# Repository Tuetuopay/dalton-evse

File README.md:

# OSS EVSE

I hope you like the daltons!

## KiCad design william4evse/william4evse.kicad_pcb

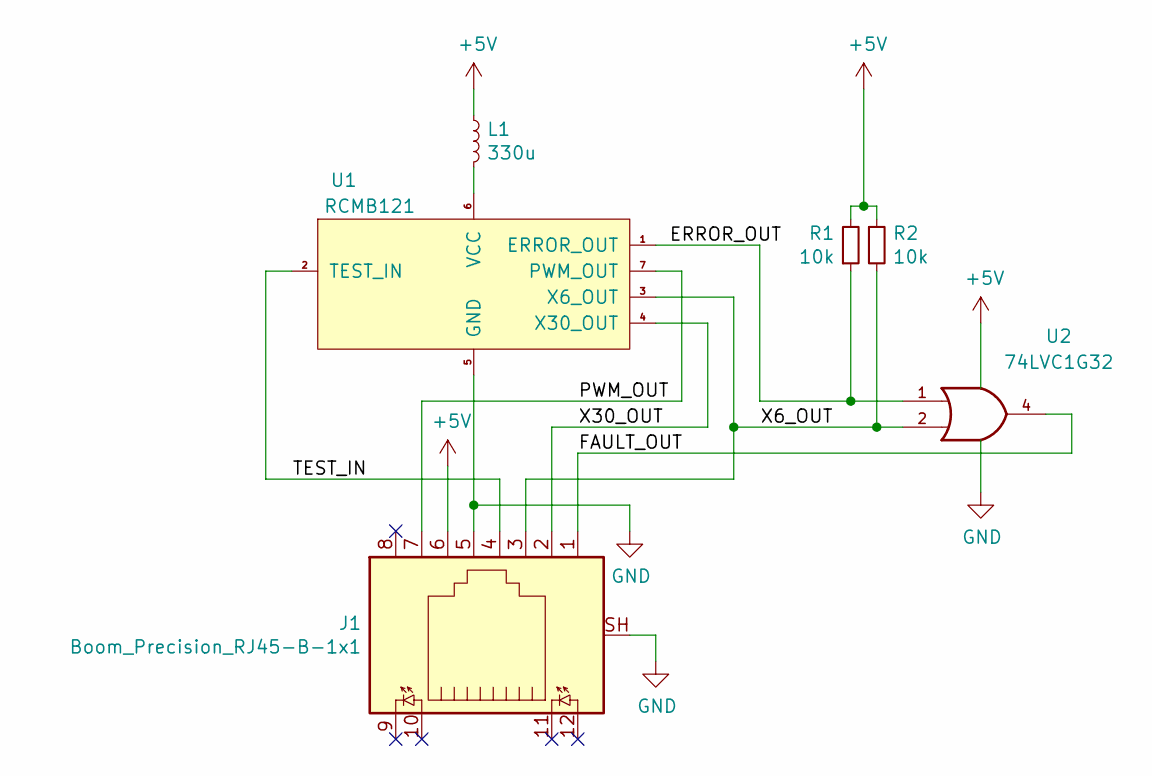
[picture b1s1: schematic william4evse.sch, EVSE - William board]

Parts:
J1: Boom_Precision_RJ45-B-1x1; RJ45_Amphenol_RJHSE538X
L1: 330u; L_1210_3225Metric; MFR P/N NLCV32T-331K-PF; LCSC P/N C87557
R1, R2: 10k; R_0603_1608Metric; MFR P/N 0603WAF1002T5E; LCSC P/N C25804
U1: RCMB121
U2: 74LVC1G32; SOT-353_SC-70-5; MFR P/N 74LVC1G32GW,125; LCSC P/N C12516

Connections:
+5V: J1.6, L1.1, R1.2, R2.1, U2.5 (VCC)
/ERROR_OUT: R1.1, U1.1 (ERROR_OUT), U2.1
/FAULT_OUT: J1.1, U2.4
/PWM_OUT: J1.7, U1.7 (PWM_OUT)
/TEST_IN: J1.4, U1.2 (TEST_IN)
/X6_OUT: J1.3, R2.2, U1.3 (X6_OUT), U2.2
/X30_OUT: J1.2, U1.4 (X30_OUT)
GND: J1.5, J1.SH, U1.5 (GND), U2.3 (GND)
unnamed: L1.2, U1.6 (VCC)

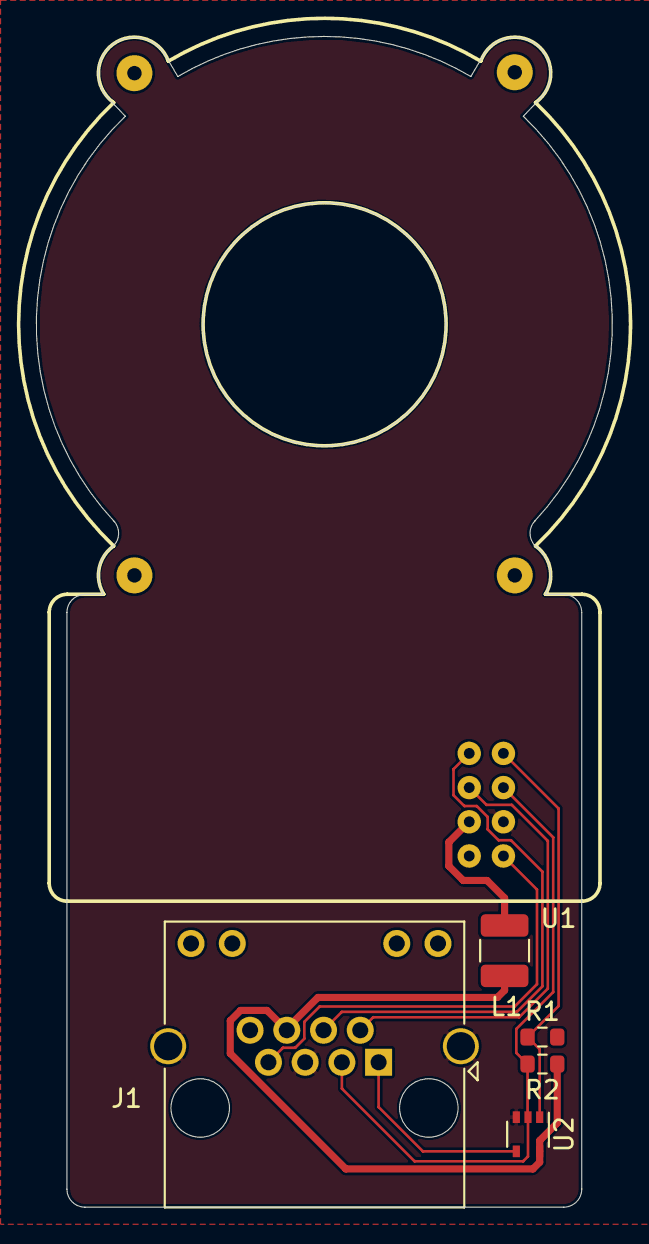
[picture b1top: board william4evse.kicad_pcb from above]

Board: 2 copper layers, 32.0 x 65.0 mm, 6 parts (0 on the bottom side), 9 nets.

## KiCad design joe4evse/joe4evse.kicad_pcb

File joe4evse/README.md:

# joe4evse

Joe, the brain of the operation. Main PCB of Daltons EVSE

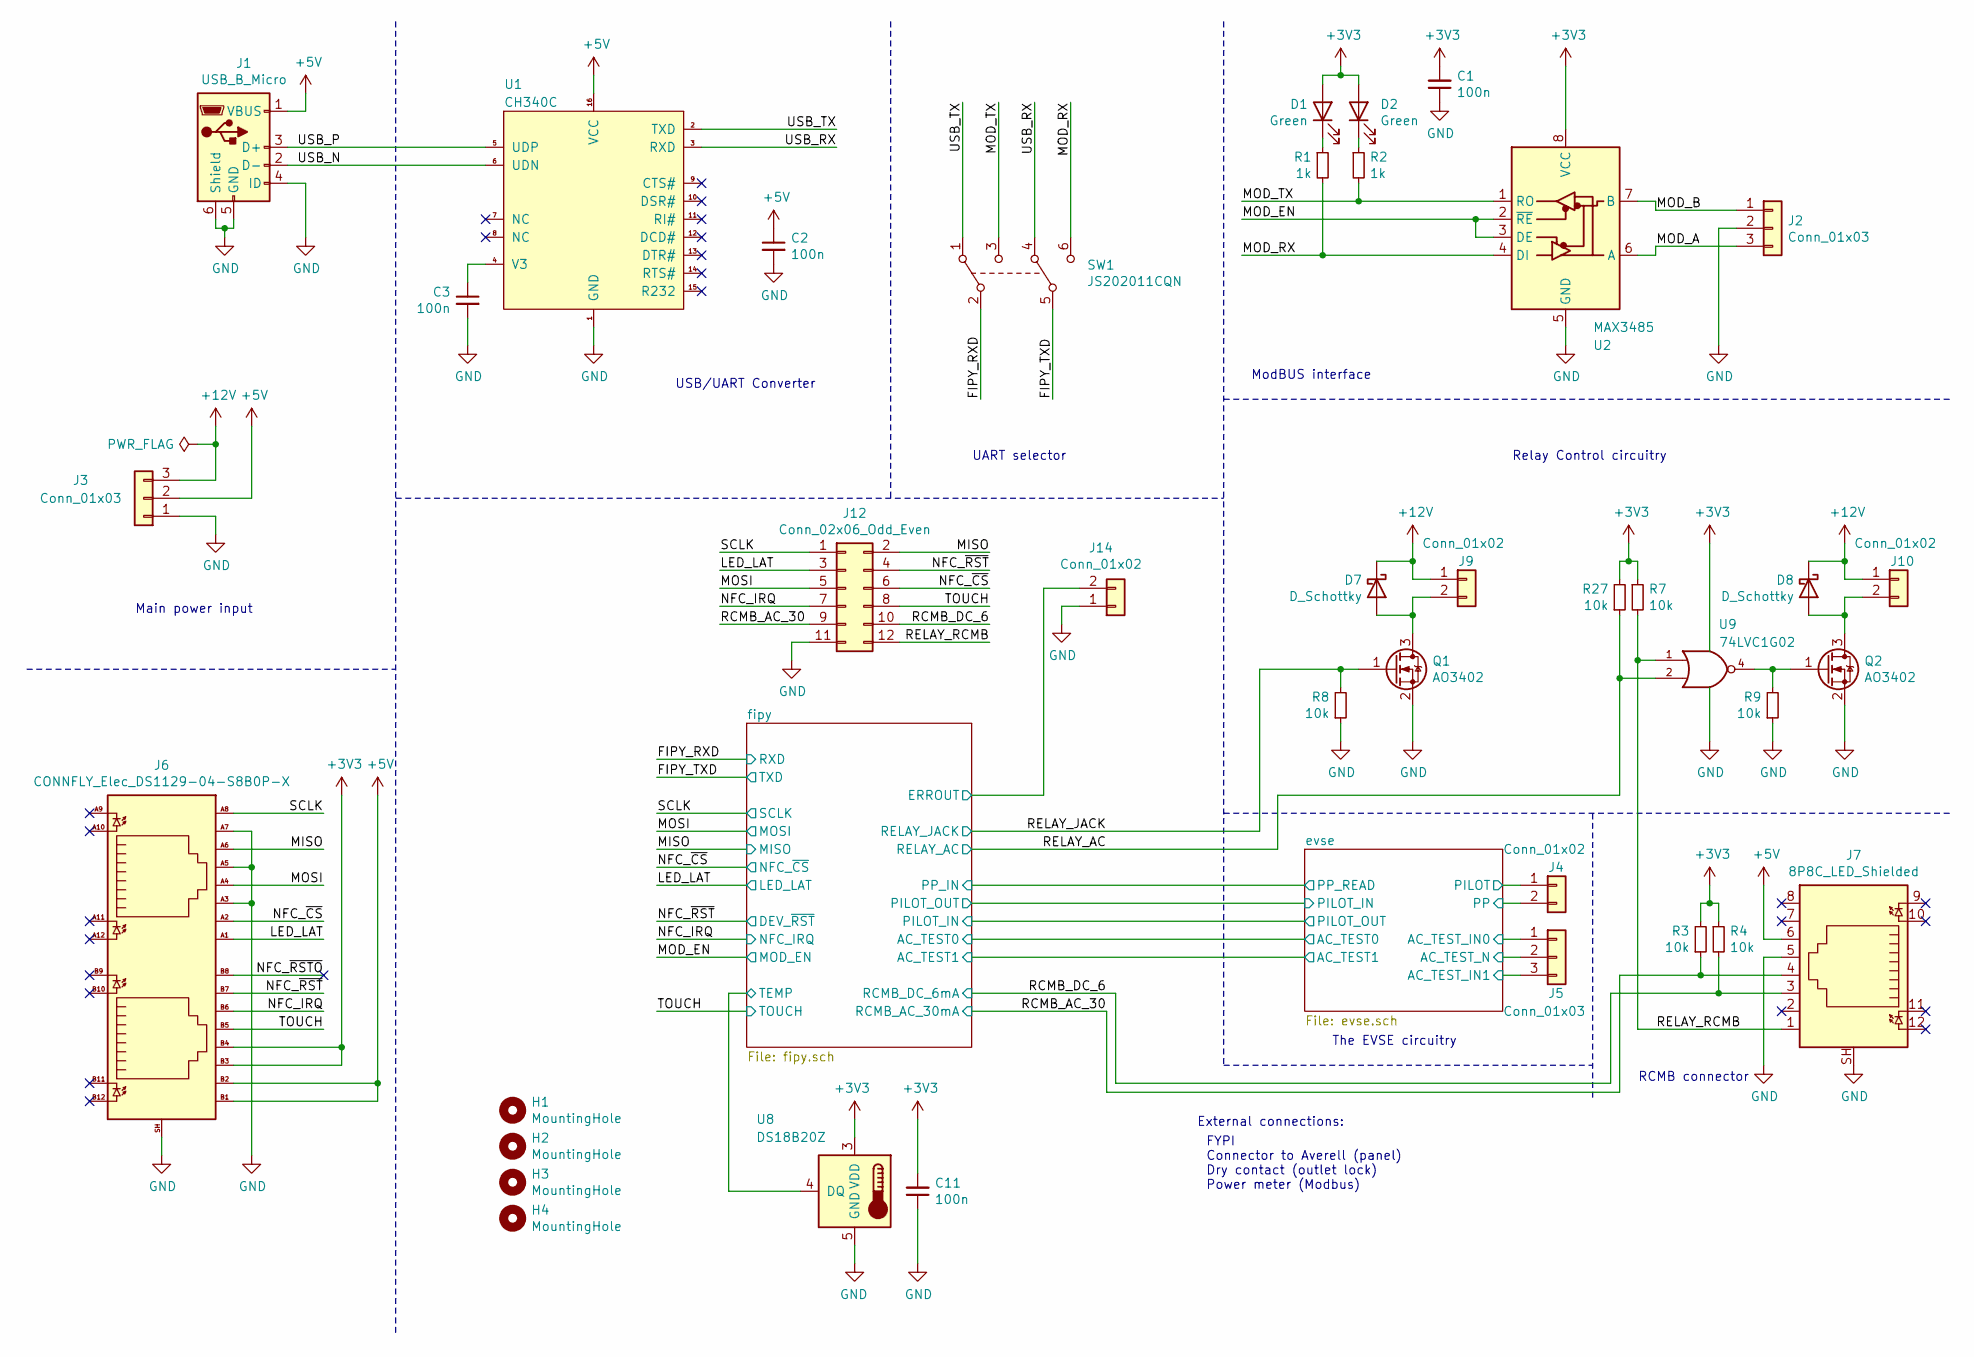
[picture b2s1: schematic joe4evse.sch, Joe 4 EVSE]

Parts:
C1, C2, C3, C11: 100n; C_0603_1608Metric
D1, D2: Green; LED_0603_1608Metric
D7, D8: D_Schottky; D_SOD-123
H1, H2, H3, H4: MountingHole; MountingHole_3.2mm_M3_Pad_Via
J1: USB_B_Micro; USB_Micro-B_Molex_47346-0001
J2: Conn_01x03; JST_PH_B3B-PH-K_1x03_P2.00mm_Vertical
J3: Conn_01x03; JST_EH_B3B-EH-A_1x03_P2.50mm_Vertical
J4, J9, J10, J14: Conn_01x02; JST_PH_B2B-PH-K_1x02_P2.00mm_Vertical
J5: Conn_01x03; JST_NV_B03P-NV_1x03_P5.00mm_Vertical
J6: CONNFLY_Elec_DS1129-04-S8B0P-X
J7: 8P8C_LED_Shielded; RJ45_Amphenol_RJHSE538X
J12: Conn_02x06_Odd_Even; PinHeader_2x06_P2.54mm_Vertical
Q1, Q2: AO3402; SOT-23
R1, R2: 1k; R_0603_1608Metric
R3, R4, R7, R8, R9, R27: 10k; R_0603_1608Metric
SW1: JS202011CQN
U1: CH340C; SOIC-16_3.9x9.9mm_P1.27mm
U2: MAX3485; SOIC-8_3.9x4.9mm_P1.27mm
U8: DS18B20Z; SOIC-8_3.9x4.9mm_P1.27mm
U9: 74LVC1G02; SOT-353_SC-70-5

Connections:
+3V3: C1.2, C11.2, D1.2 (A), D2.2 (A), J6.B3, J6.B4, R3.2, R4.1, R7.1, R27.2, U2.8 (VCC), U8.3 (VDD), U9.5 (VCC); also elsewhere on the board
+5V: C2.1, J1.1 (VBUS), J3.2, J6.B1, J6.B2, J7.6, U1.16 (VCC); also elsewhere on the board
+12V: D7.1 (K), D8.1 (K), J3.3, J9.1, J10.1; also elsewhere on the board
/FIPY_RXD: SW1.2 (B1); also elsewhere on the board
/FIPY_TXD: SW1.5 (B2); also elsewhere on the board
/LED_LAT: J6.A1, J12.3; also elsewhere on the board
/MISO: J6.A6, J12.2; also elsewhere on the board
/MOD_A: J2.3, U2.6 (A)
/MOD_B: J2.1, U2.7 (B)
/MOD_EN: U2.2 (~RE), U2.3 (DE); also elsewhere on the board
/MOD_RX: R1.2, SW1.6 (C2), U2.4 (DI)
/MOD_TX: R2.2, SW1.3 (C1), U2.1 (RO)
/MOSI: J6.A4, J12.5; also elsewhere on the board
/NFC_IRQ: J6.B6, J12.7; also elsewhere on the board
/NFC_~CS: J6.A2, J12.6; also elsewhere on the board
/NFC_~RST: J6.B7, J12.4; also elsewhere on the board
/NFC_~RSTO: J6.B8
/RCMB_AC_30: J7.4, J12.9, R3.1; also elsewhere on the board
/RCMB_DC_6: J7.3, J12.10, R4.2; also elsewhere on the board
/RELAY_AC: R27.1, U9.2; also elsewhere on the board
/RELAY_JACK: Q1.1 (G), R8.2; also elsewhere on the board
/RELAY_RCMB: J7.1, J12.12, R7.2, U9.1
/SCLK: J6.A8, J12.1; also elsewhere on the board
/TOUCH: J6.B5, J12.8; also elsewhere on the board
/USB_N: J1.2 (D-), U1.6 (UDN)
/USB_P: J1.3 (D+), U1.5 (UDP)
/USB_RX: SW1.4 (A2), U1.3 (RXD)
/USB_TX: SW1.1 (A1), U1.2 (TXD)
/evse/AC_TEST_IN0: J5.1; also elsewhere on the board
/evse/AC_TEST_IN1: J5.3; also elsewhere on the board
/evse/AC_TEST_N: J5.2; also elsewhere on the board
/evse/PILOT: J4.1; also elsewhere on the board
/evse/PP: J4.2; also elsewhere on the board
/fipy/ERROUT: J14.2; also elsewhere on the board
/fipy/TEMP: U8.4 (DQ); also elsewhere on the board
GND: C1.1, C2.2, C3.2, C11.1, J1.4 (ID), J1.5 (GND), J1.6 (Shield), J2.2, J3.1, J6.A3, J6.A5, J6.A7, J6.SH, J7.5, J7.SH, J12.11, J14.1, Q1.2 (S), Q2.2 (S), R8.1, R9.1, U1.1 (GND), U2.5 (GND), U8.5 (GND), U9.3 (GND); also elsewhere on the board
unnamed: C3.1, U1.4 (V3)
unnamed: D1.1 (K), R1.1
unnamed: D2.1 (K), R2.1
unnamed: D7.2 (A), J9.2, Q1.3 (D)
unnamed: D8.2 (A), J10.2, Q2.3 (D)
unnamed: Q2.1 (G), R9.2, U9.4

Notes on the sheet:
Main power input
USB/UART Converter
UART selector
ModBUS interface
External connections:
FYPI Connector to Averell (panel) Dry contact (outlet lock) Power meter (Modbus)
RCMB connector
The EVSE circuitry
Relay Control circuitry

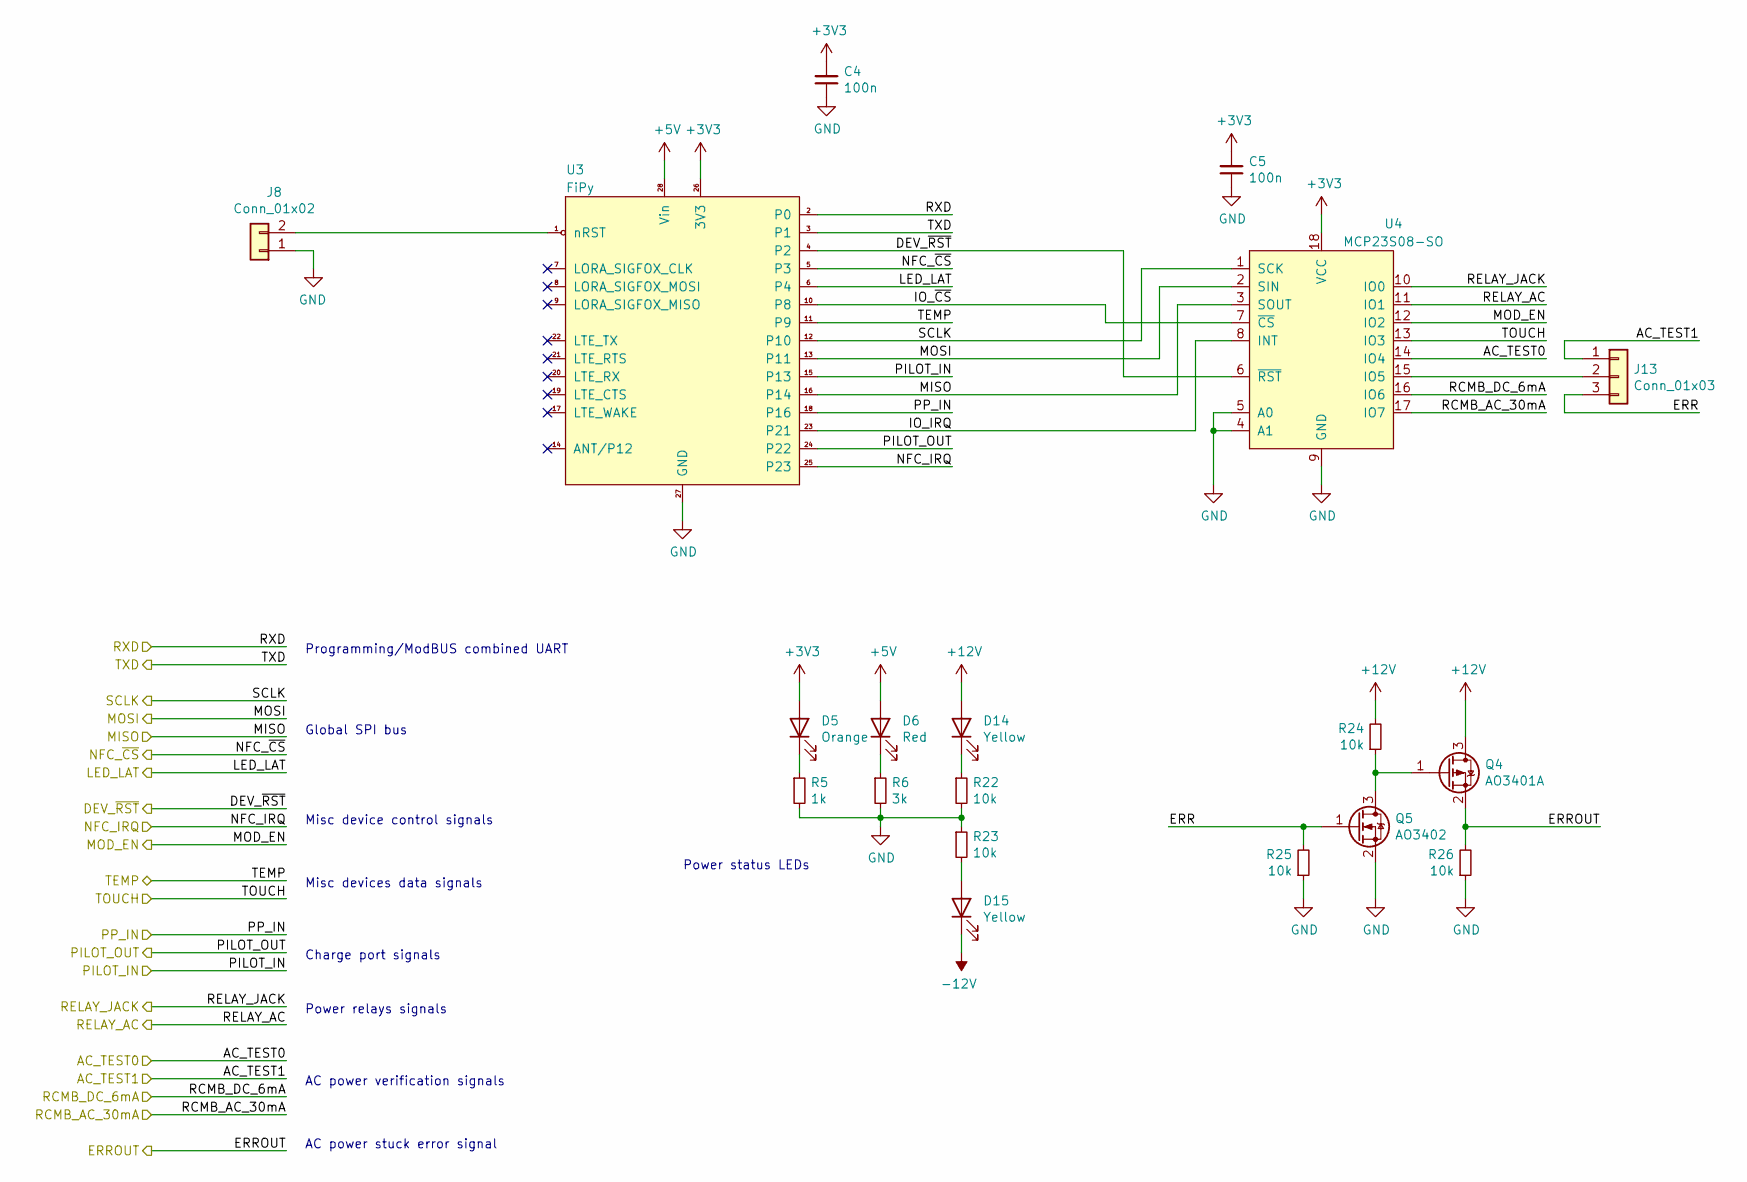
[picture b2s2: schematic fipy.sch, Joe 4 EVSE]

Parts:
C4, C5: 100n; C_0603_1608Metric
D5: Orange; LED_0603_1608Metric
D6: Red; LED_0603_1608Metric
D14, D15: Yellow; LED_0603_1608Metric
J8: Conn_01x02; PinHeader_1x02_P2.54mm_Vertical
J13: Conn_01x03; PinHeader_1x03_P2.54mm_Vertical
Q4: AO3401A; SOT-23
Q5: AO3402; SOT-23
R5: 1k; R_0603_1608Metric
R6: 3k; R_0603_1608Metric
R22, R23, R24, R25, R26: 10k; R_0603_1608Metric
U3: FiPy; fipy
U4: MCP23S08-SO; SOIC-18W_7.5x11.6mm_P1.27mm

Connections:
+3V3: C4.2, C5.2, D5.2 (A), U3.26 (3V3), U4.18 (VCC); also elsewhere on the board
+5V: D6.2 (A), U3.28 (Vin); also elsewhere on the board
+12V: D14.2 (A), Q4.3 (D), R24.2; also elsewhere on the board
-12V: D15.1 (K); also elsewhere on the board
/FIPY_RXD: U3.2 (P0); also elsewhere on the board
/FIPY_TXD: U3.3 (P1); also elsewhere on the board
/LED_LAT: U3.6 (P4); also elsewhere on the board
/MISO: U3.16 (P14), U4.3 (SOUT); also elsewhere on the board
/MOD_EN: U4.12 (IO2); also elsewhere on the board
/MOSI: U3.13 (P11), U4.2 (SIN); also elsewhere on the board
/NFC_IRQ: U3.25 (P23); also elsewhere on the board
/NFC_~CS: U3.5 (P3); also elsewhere on the board
/NFC_~RST: U3.4 (P2), U4.6 (~RST); also elsewhere on the board
/RCMB_AC_30: U4.17 (IO7); also elsewhere on the board
/RCMB_DC_6: U4.16 (IO6); also elsewhere on the board
/RELAY_AC: U4.11 (IO1); also elsewhere on the board
/RELAY_JACK: U4.10 (IO0); also elsewhere on the board
/SCLK: U3.12 (P10), U4.1 (SCK); also elsewhere on the board
/TOUCH: U4.13 (IO3); also elsewhere on the board
/evse/AC_TEST0: U4.14 (IO4); also elsewhere on the board
/evse/AC_TEST1: J13.1; also elsewhere on the board
/evse/PILOT_IN: U3.24 (P22); also elsewhere on the board
/fipy/ERR: J13.3, Q5.1 (G), R25.2
/fipy/ERROUT: Q4.2 (S), R26.2; also elsewhere on the board
/fipy/IO_IRQ: U3.23 (P21), U4.8 (INT)
/fipy/IO_~CS: U3.10 (P8), U4.7 (~CS)
/fipy/PILOT_IN: U3.15 (P13); also elsewhere on the board
/fipy/PP_IN: U3.18 (P16); also elsewhere on the board
/fipy/TEMP: U3.11 (P9); also elsewhere on the board
GND: C4.1, C5.1, J8.1, Q5.2 (S), R5.2, R6.2, R22.2, R23.1, R25.1, R26.1, U3.27 (GND), U4.4 (A1), U4.5 (A0), U4.9 (GND); also elsewhere on the board
unnamed: D5.1 (K), R5.1
unnamed: D6.1 (K), R6.1
unnamed: D14.1 (K), R22.1
unnamed: D15.2 (A), R23.2
unnamed: J8.2, U3.1 (nRST)
unnamed: J13.2, U4.15 (IO5)
unnamed: Q4.1 (G), Q5.3 (D), R24.1

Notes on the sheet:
Programming/ModBUS combined UART
Global SPI bus
Misc device control signals
Misc devices data signals
Charge port signals
Power relays signals
AC power verification signals
Power status LEDs
AC power stuck error signal

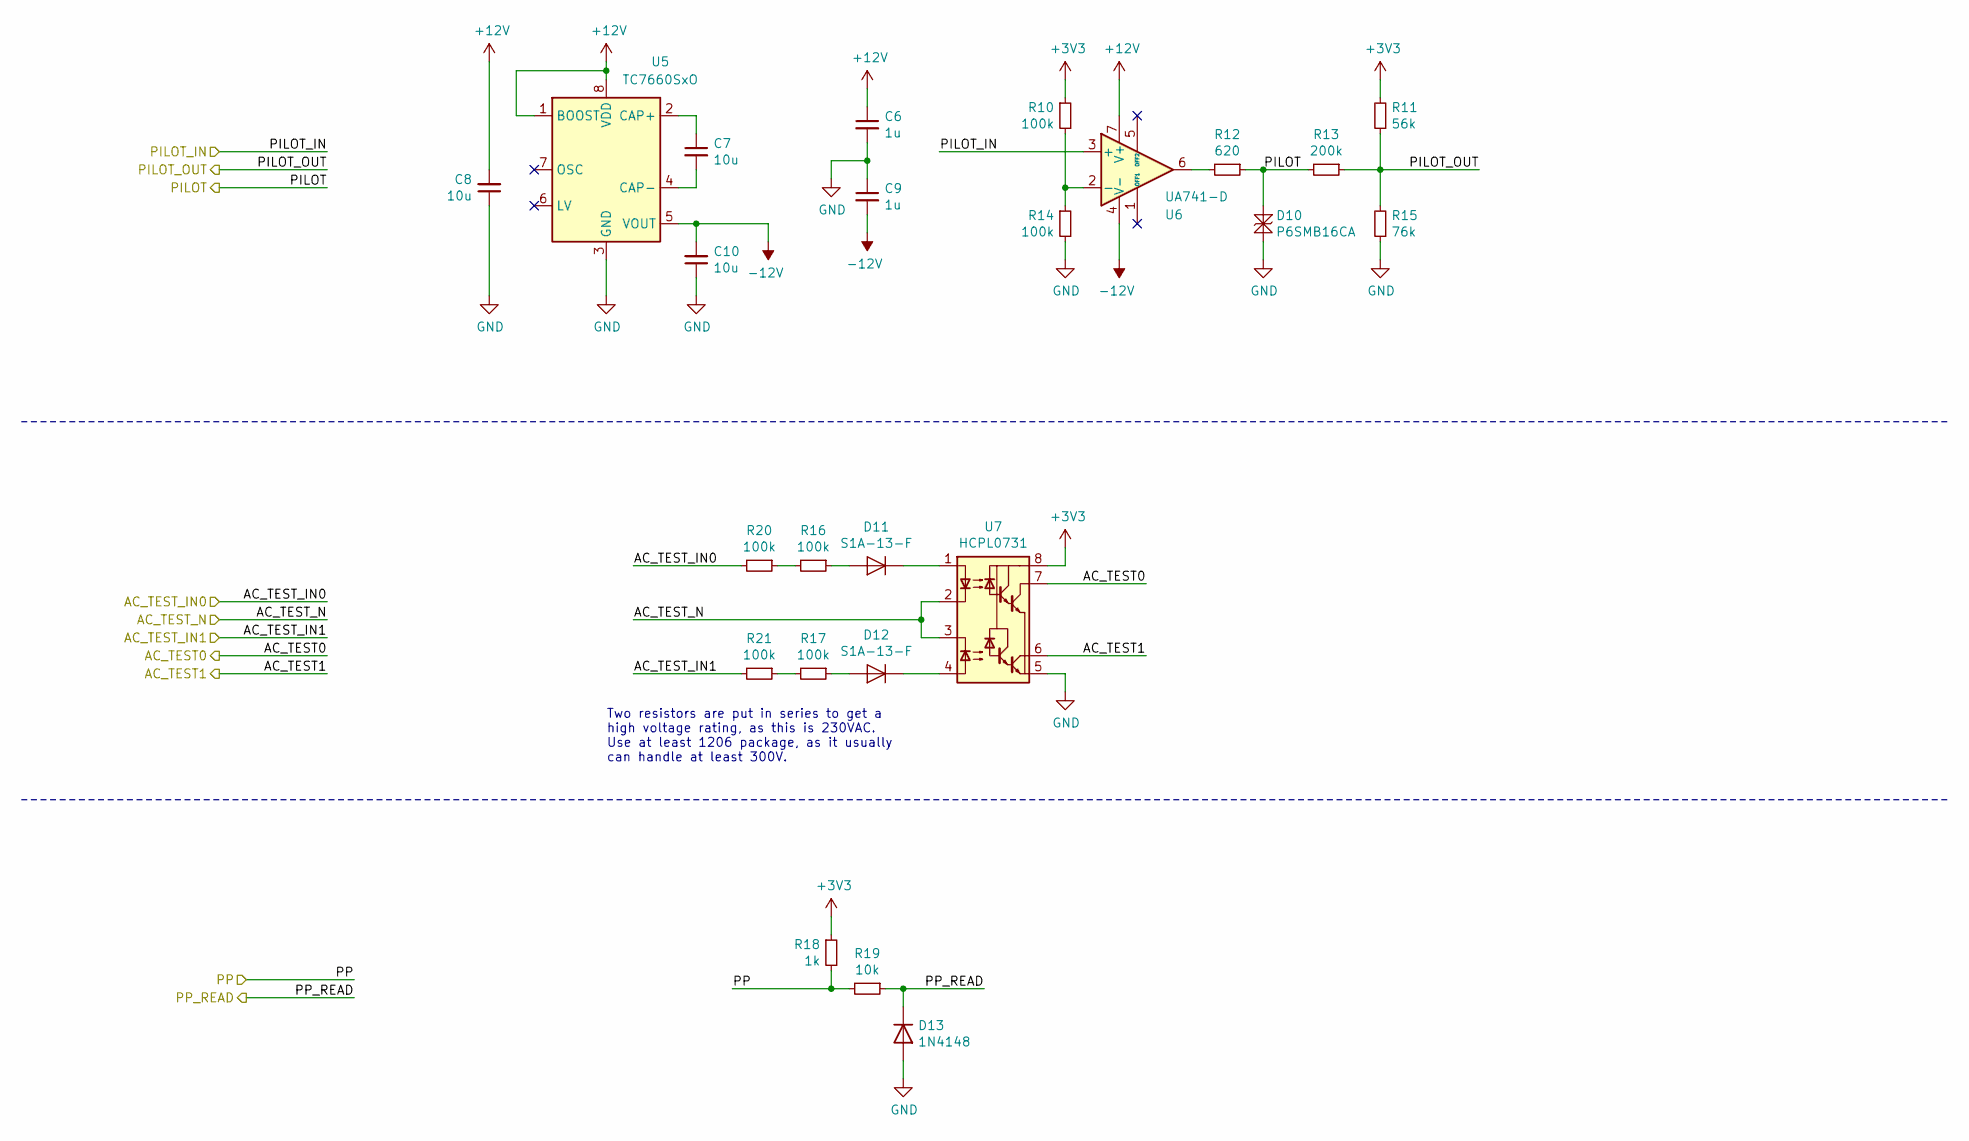
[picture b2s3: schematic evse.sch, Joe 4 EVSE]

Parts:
C6, C9: 1u; C_0603_1608Metric
C7, C8, C10: 10u; C_0805_2012Metric
D10: P6SMB16CA; D_SMB
D11, D12: S1A-13-F; D_SMA
D13: 1N4148; D_SOD-123
R10, R14: 100k; R_0603_1608Metric
R11: 56k; R_0603_1608Metric
R12: 620; R_0603_1608Metric
R13: 200k; R_0603_1608Metric
R15: 76k; R_0603_1608Metric
R16, R17, R20, R21: 100k; R_1206_3216Metric
R18: 1k; R_0603_1608Metric
R19: 10k; R_0603_1608Metric
U5: TC7660SxO; SOIC-8_3.9x4.9mm_P1.27mm
U6: UA741-D; SOIC-8_3.9x4.9mm_P1.27mm; Manufacturer PN uA741-D
U7: HCPL0731; SOIC-8_3.9x4.9mm_P1.27mm; Manufacturer PN HCPL0731

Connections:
+3V3: R10.1, R11.2, R18.1, U7.8 (VCC); also elsewhere on the board
+12V: C6.1, C8.2, U5.1 (BOOST), U5.8 (VDD), U6.7 (V+); also elsewhere on the board
-12V: C9.2, C10.2, U5.5 (VOUT), U6.4 (V-); also elsewhere on the board
/evse/AC_TEST0: U7.7 (VO1); also elsewhere on the board
/evse/AC_TEST1: U7.6 (VO2); also elsewhere on the board
/evse/AC_TEST_IN0: R20.2; also elsewhere on the board
/evse/AC_TEST_IN1: R21.2; also elsewhere on the board
/evse/AC_TEST_N: U7.2 (C1), U7.3 (C2); also elsewhere on the board
/evse/PILOT: D10.1 (K), R12.1, R13.2; also elsewhere on the board
/evse/PILOT_IN: U6.3 (+); also elsewhere on the board
/evse/PP: R18.2, R19.2; also elsewhere on the board
/fipy/PILOT_IN: R11.1, R13.1, R15.2; also elsewhere on the board
/fipy/PP_IN: D13.1 (K), R19.1; also elsewhere on the board
GND: C6.2, C8.1, C9.1, C10.1, D10.2 (A), D13.2 (A), R14.2, R15.1, U5.3 (GND), U7.5 (GND); also elsewhere on the board
unnamed: C7.1, U5.2 (CAP+)
unnamed: C7.2, U5.4 (CAP-)
unnamed: D11.1 (K), U7.1 (A1)
unnamed: D11.2 (A), R16.1
unnamed: D12.1 (K), U7.4 (A2)
unnamed: D12.2 (A), R17.1
unnamed: R10.2, R14.1, U6.2 (-)
unnamed: R12.2, U6.6
unnamed: R16.2, R20.1
unnamed: R17.2, R21.1

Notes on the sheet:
Two resistors are put in series to get a high voltage rating, as this is 230VAC. Use at least 1206 package, as it usually can handle at least 300V.

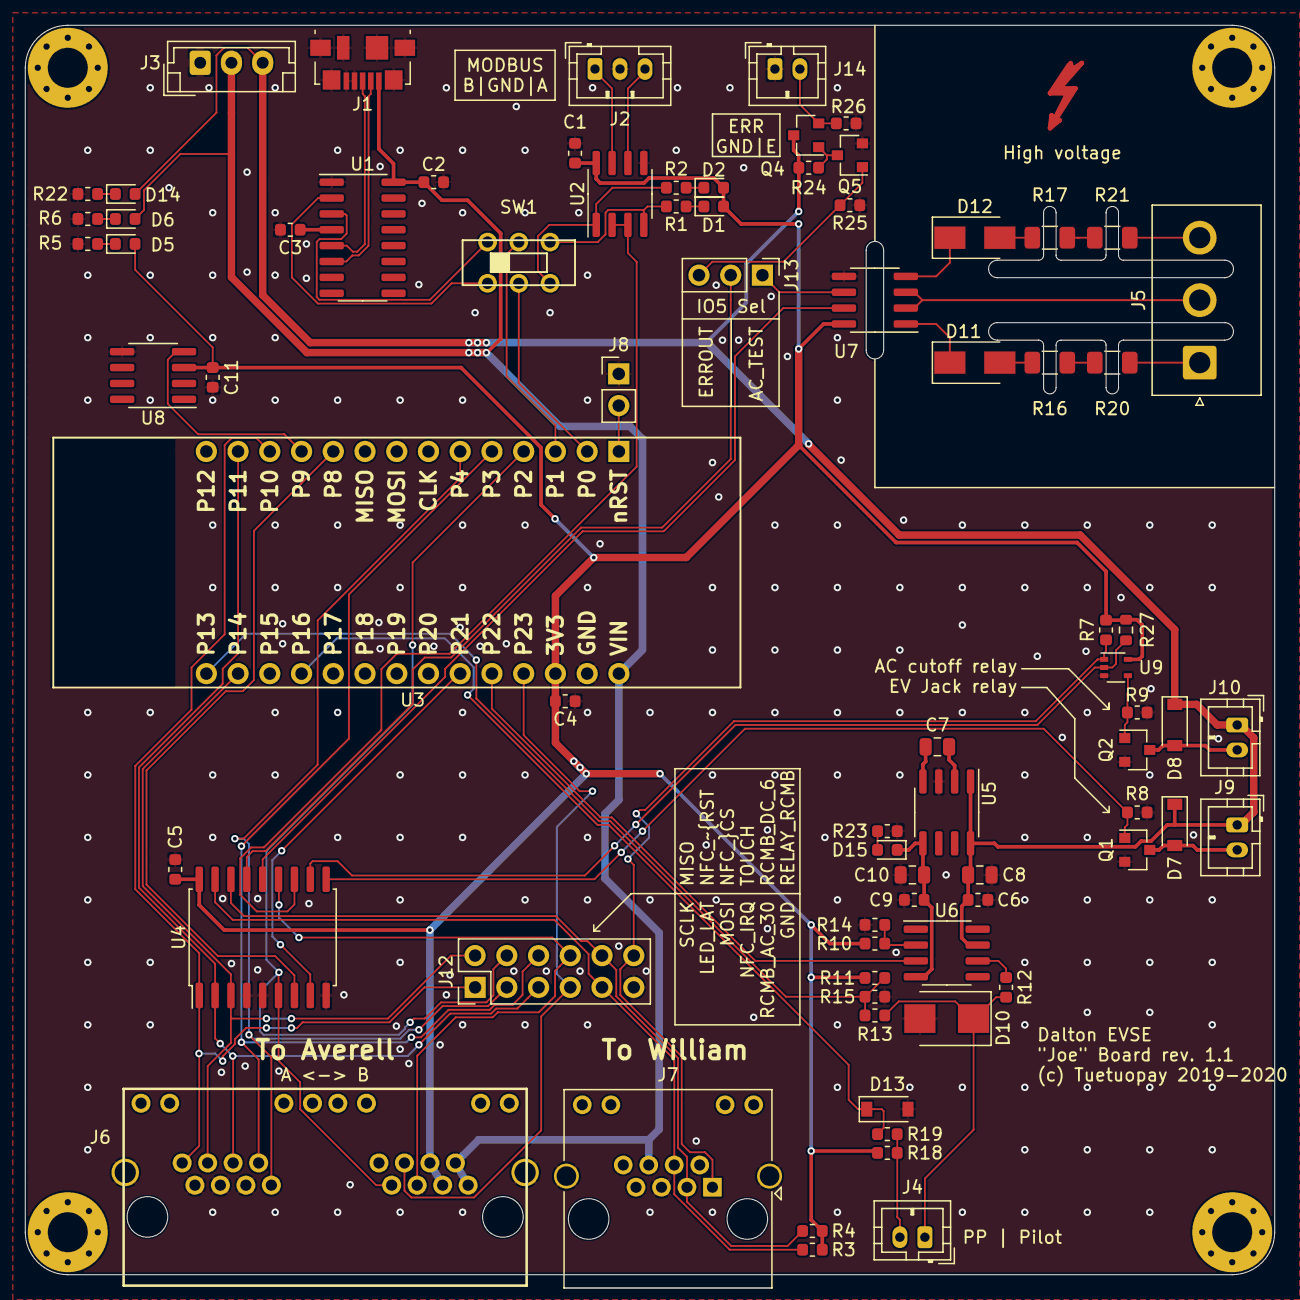
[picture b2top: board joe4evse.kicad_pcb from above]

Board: 2 copper layers, 100.0 x 100.0 mm, 81 parts (0 on the bottom side), 67 nets.

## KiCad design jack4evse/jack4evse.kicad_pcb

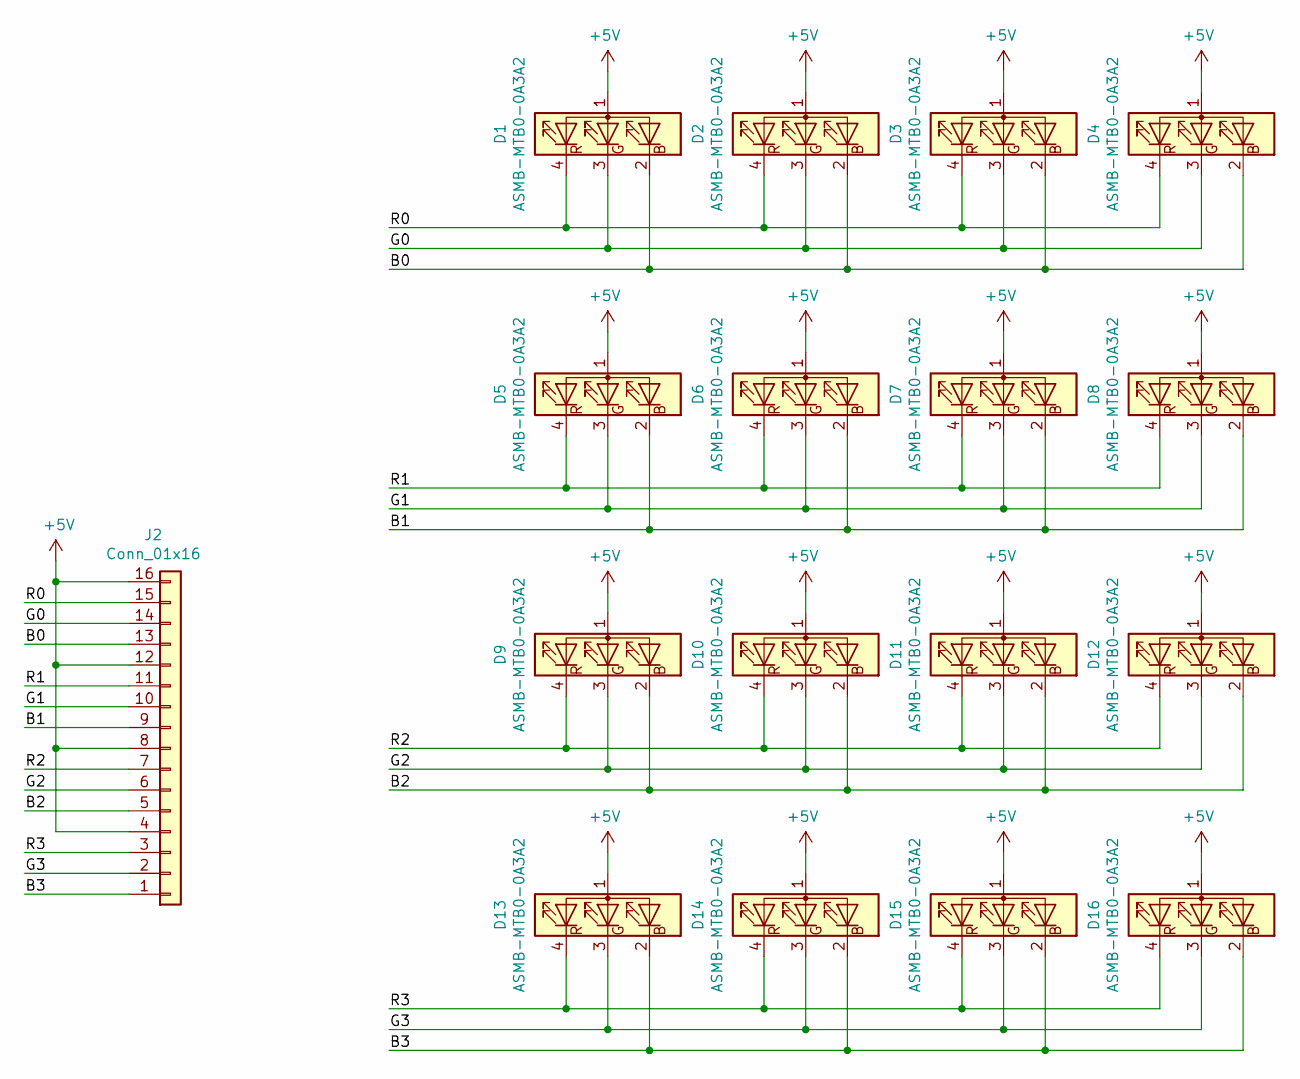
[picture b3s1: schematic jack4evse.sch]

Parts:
D1, D2, D3, D4, D5, D6, D7, D8, D9, D10, D11, D12, D13, D14, D15, D16: ASMB-MTB0-0A3A2; LED_Avago_PLCC4_3.2x2.8mm_CW
J2: Conn_01x16; PinHeader_1x16_P2.54mm_Horizontal

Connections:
+5V: D1.1 (A), D2.1 (A), D3.1 (A), D4.1 (A), D5.1 (A), D6.1 (A), D7.1 (A), D8.1 (A), D9.1 (A), D10.1 (A), D11.1 (A), D12.1 (A), D13.1 (A), D14.1 (A), D15.1 (A), D16.1 (A), J2.4, J2.8, J2.12, J2.16
/B0: D1.2 (BK), D2.2 (BK), D3.2 (BK), D4.2 (BK), J2.13
/B1: D5.2 (BK), D6.2 (BK), D7.2 (BK), D8.2 (BK), J2.9
/B2: D9.2 (BK), D10.2 (BK), D11.2 (BK), D12.2 (BK), J2.5
/B3: D13.2 (BK), D14.2 (BK), D15.2 (BK), D16.2 (BK), J2.1
/G0: D1.3 (GK), D2.3 (GK), D3.3 (GK), D4.3 (GK), J2.14
/G1: D5.3 (GK), D6.3 (GK), D7.3 (GK), D8.3 (GK), J2.10
/G2: D9.3 (GK), D10.3 (GK), D11.3 (GK), D12.3 (GK), J2.6
/G3: D13.3 (GK), D14.3 (GK), D15.3 (GK), D16.3 (GK), J2.2
/R0: D1.4 (RK), D2.4 (RK), D3.4 (RK), D4.4 (RK), J2.15
/R1: D5.4 (RK), D6.4 (RK), D7.4 (RK), D8.4 (RK), J2.11
/R2: D9.4 (RK), D10.4 (RK), D11.4 (RK), D12.4 (RK), J2.7
/R3: D13.4 (RK), D14.4 (RK), D15.4 (RK), D16.4 (RK), J2.3

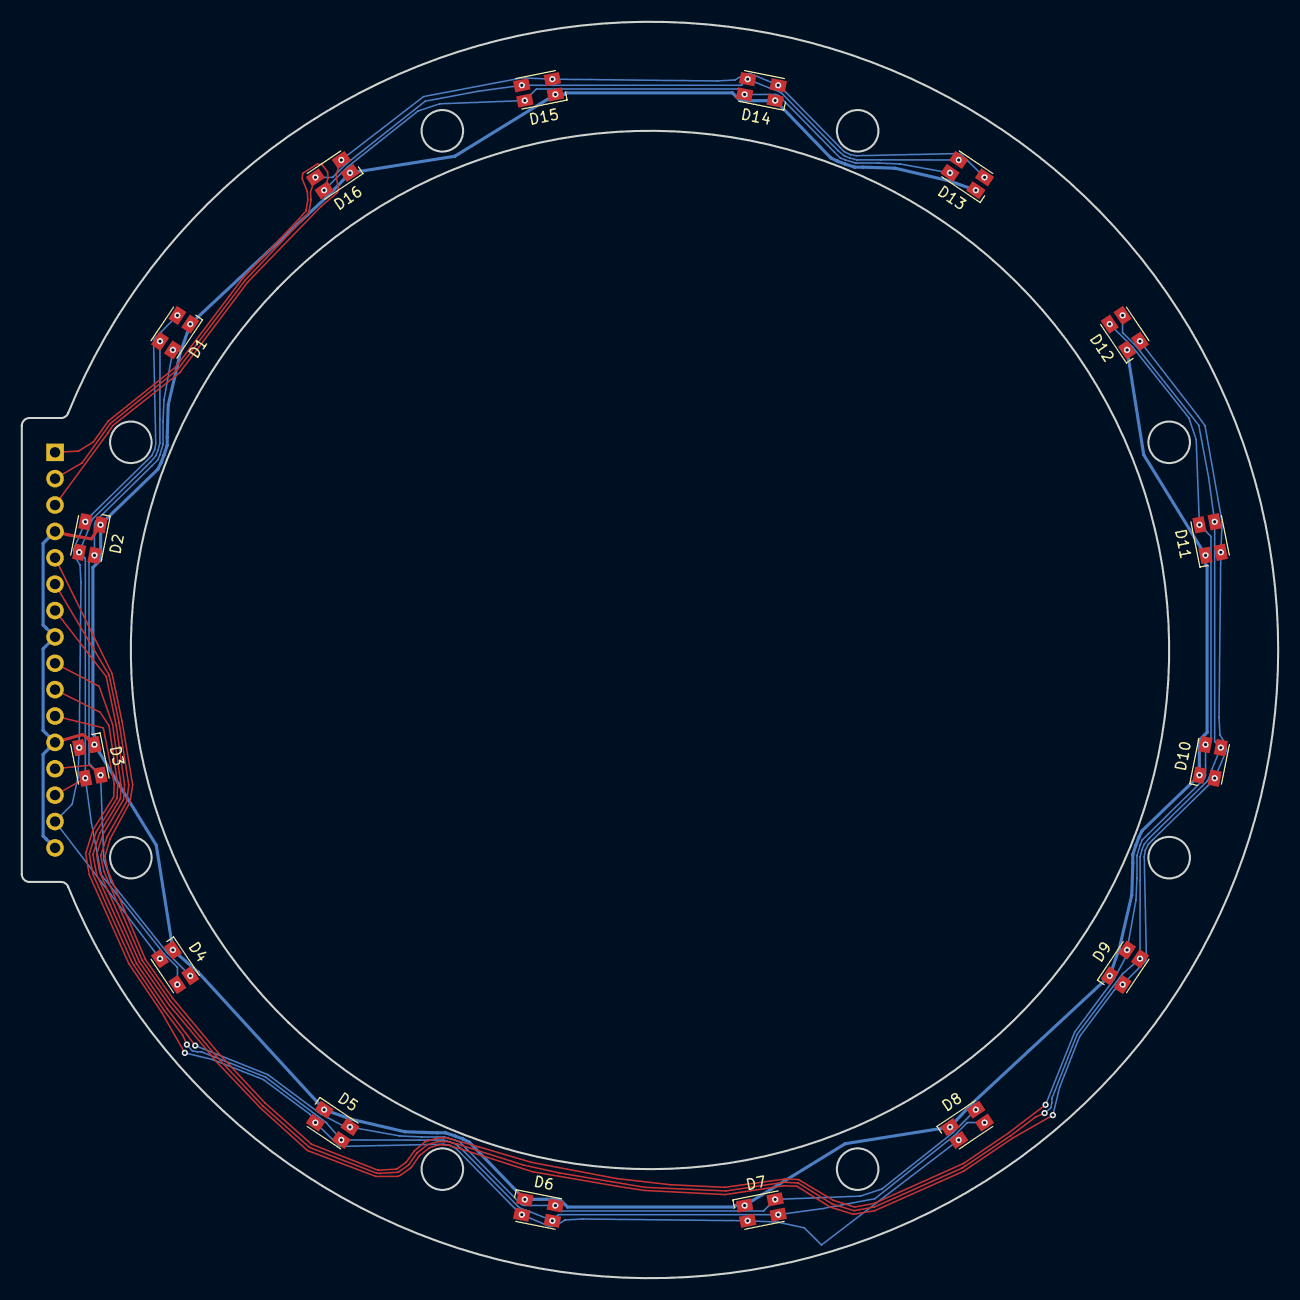
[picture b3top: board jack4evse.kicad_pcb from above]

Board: 2 copper layers, 121.0 x 121.0 mm, 17 parts (1 on the bottom side), 13 nets.
